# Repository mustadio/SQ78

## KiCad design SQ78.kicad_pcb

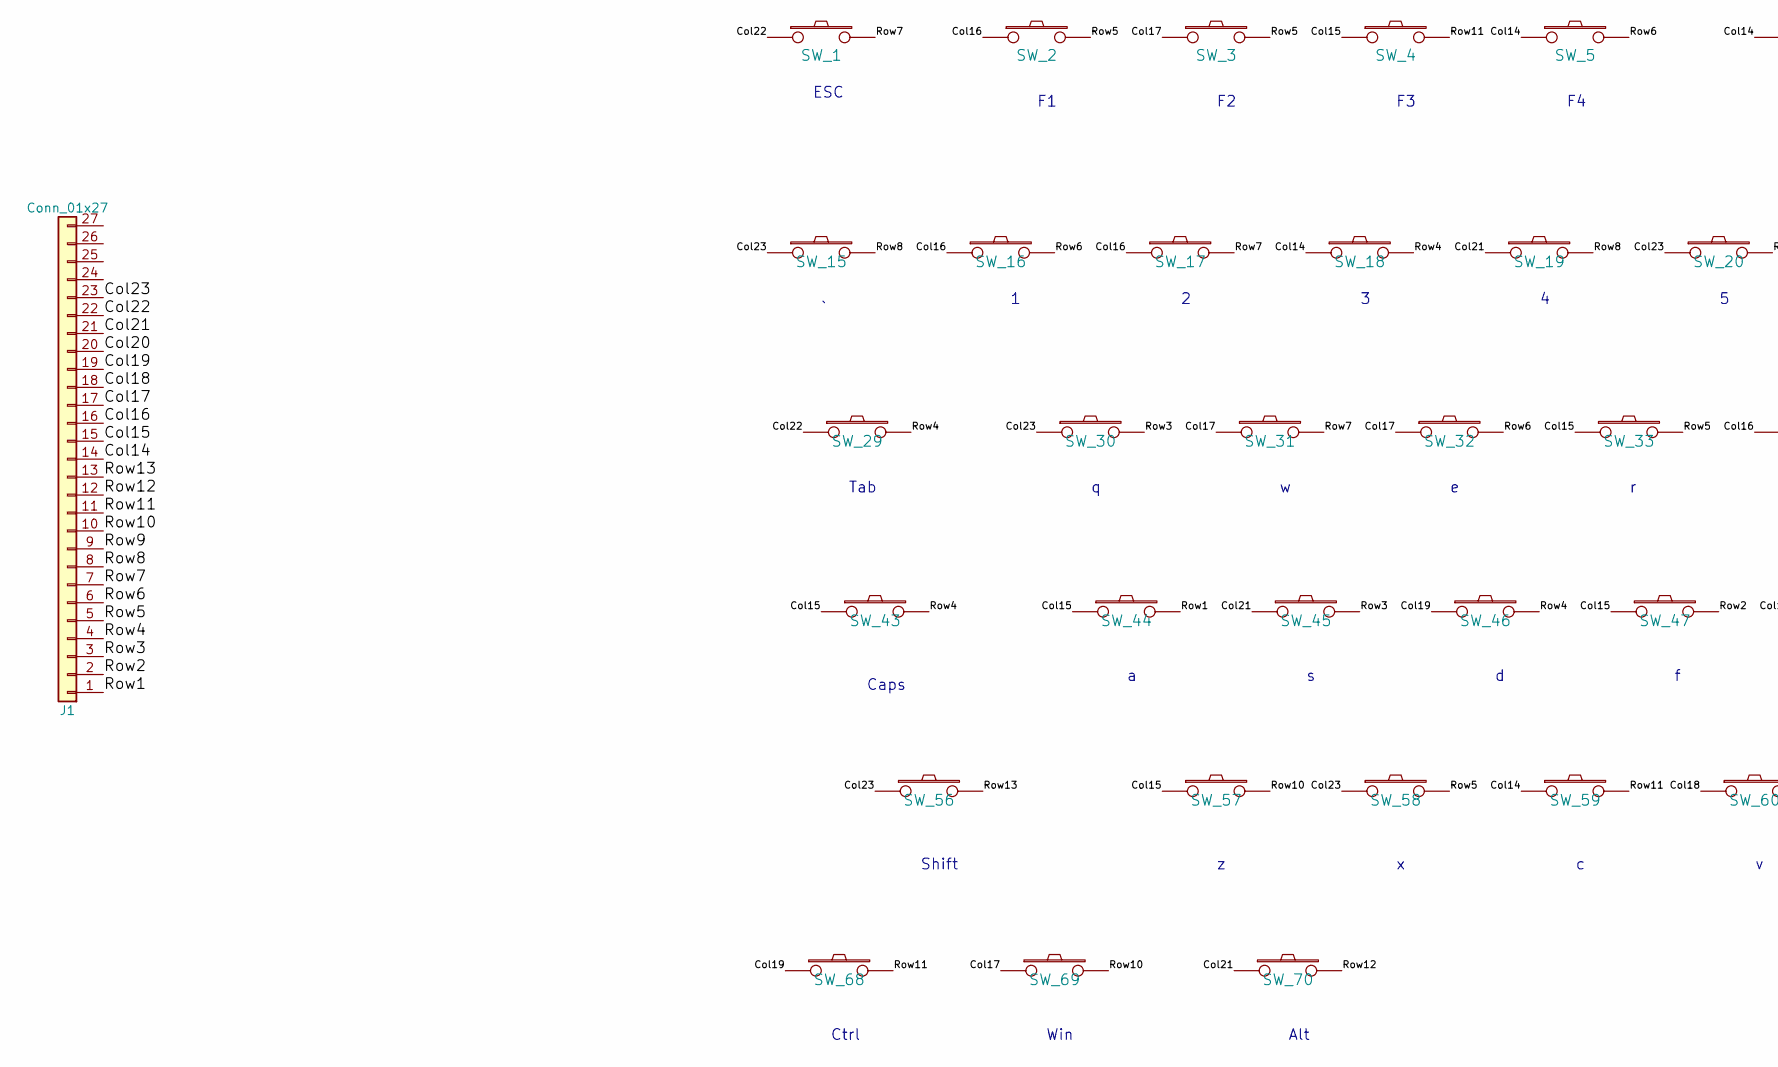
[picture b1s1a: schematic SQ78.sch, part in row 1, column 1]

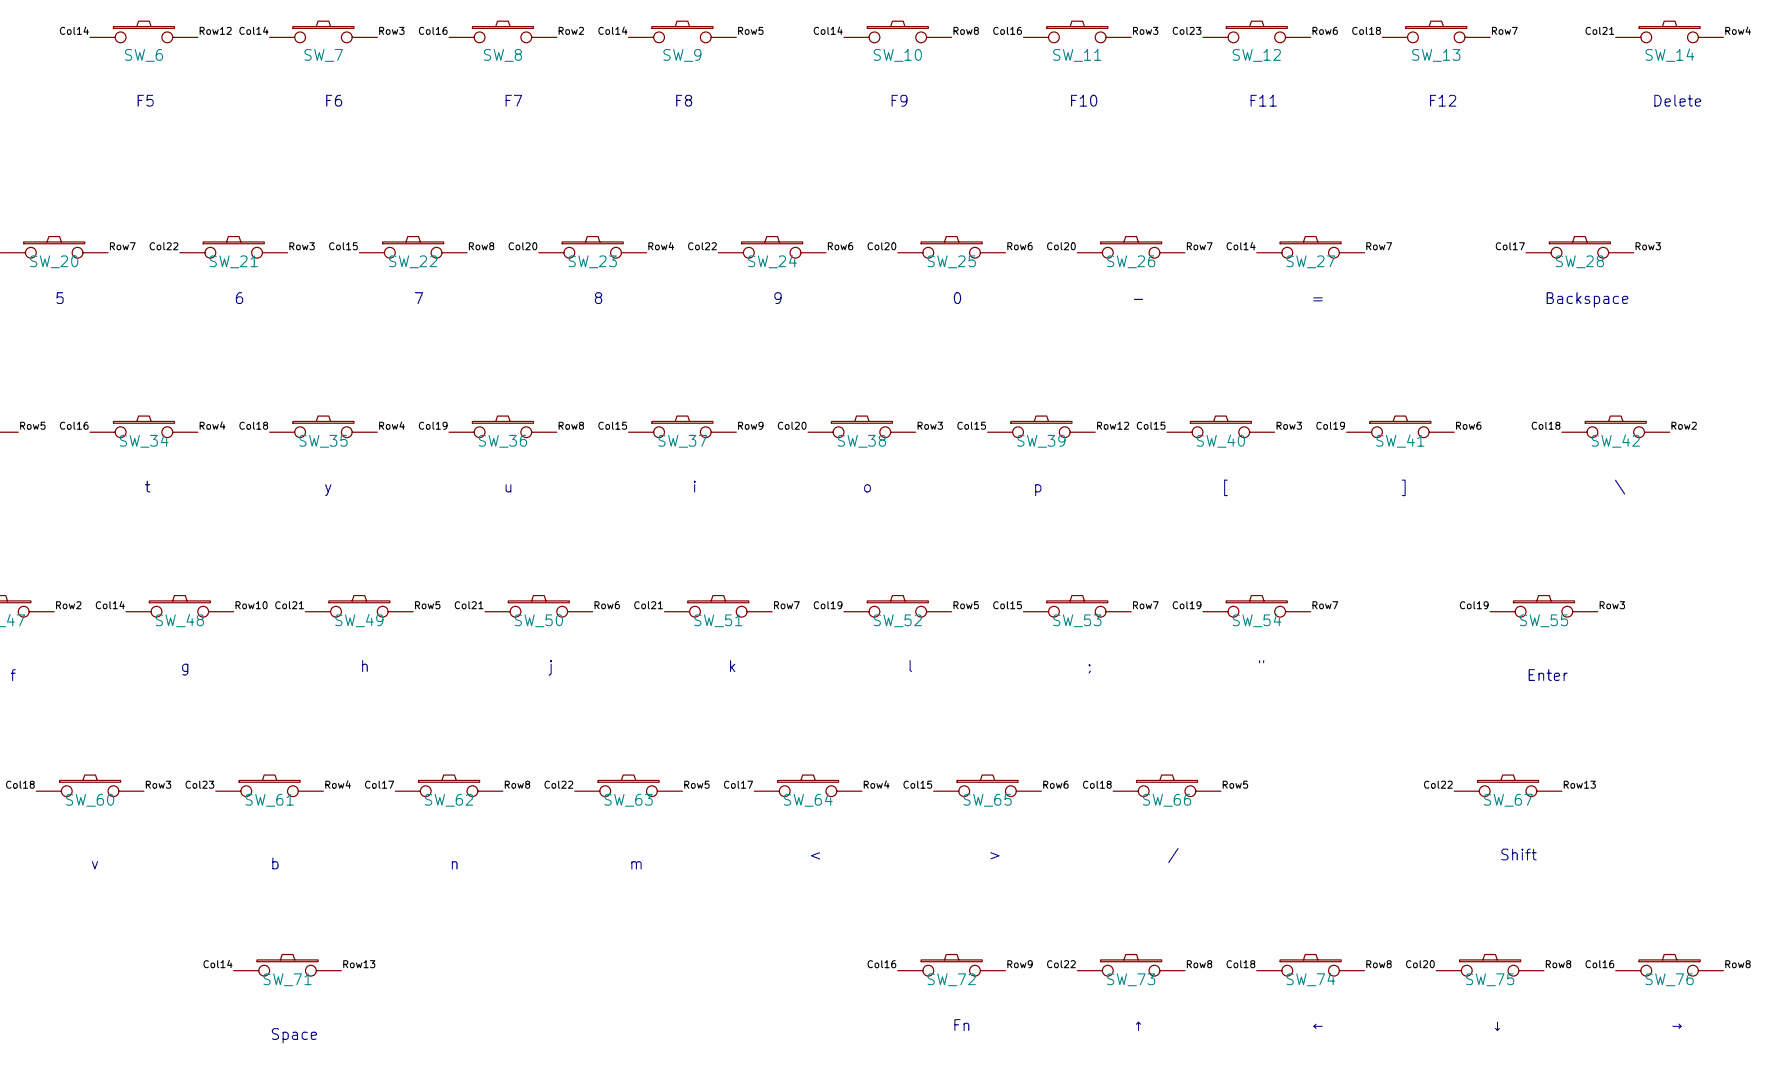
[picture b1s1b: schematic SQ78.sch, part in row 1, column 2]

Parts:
J1: Conn_01x27; TE_2-84953-7_1x27-1MP_P1.0mm_Horizontal
SW_1: ESC; CHERRY_PCB_100H
SW_2: F1; CHERRY_PCB_100H
SW_3: F2; CHERRY_PCB_100H
SW_4: F3; CHERRY_PCB_100H
SW_5: F4; CHERRY_PCB_100H
SW_6: F5; CHERRY_PCB_100H
SW_7: F6; CHERRY_PCB_100H
SW_8: F7; CHERRY_PCB_100H
SW_9: F8; CHERRY_PCB_100H
SW_10: F9; CHERRY_PCB_100H
SW_11: F10; CHERRY_PCB_100H
SW_12: F11; CHERRY_PCB_100H
SW_13: F12; CHERRY_PCB_100H
SW_14: Delete; CHERRY_PCB_100H
SW_15: CHERRY_PCB_100H
SW_16: 1; CHERRY_PCB_100H
SW_17: 2; CHERRY_PCB_100H
SW_18: 3; CHERRY_PCB_100H
SW_19: 4; CHERRY_PCB_100H
SW_20: 5; CHERRY_PCB_100H
SW_21: 6; CHERRY_PCB_100H
SW_22: 7; CHERRY_PCB_100H
SW_23: 8; CHERRY_PCB_100H
SW_24: 9; CHERRY_PCB_100H
SW_25: 0; CHERRY_PCB_100H
SW_26: -; CHERRY_PCB_100H
SW_27: =; CHERRY_PCB_100H
SW_28: Backspace; CHERRY_PCB_100H
SW_29: Tab; CHERRY_PCB_100H
SW_30: Q; CHERRY_PCB_100H
SW_31: W; CHERRY_PCB_100H
SW_32: E; CHERRY_PCB_100H
SW_33: R; CHERRY_PCB_100H
SW_34: T; CHERRY_PCB_100H
SW_35: Y; CHERRY_PCB_100H
SW_36: U; CHERRY_PCB_100H
SW_37: I; CHERRY_PCB_100H
SW_38: O; CHERRY_PCB_100H
SW_39: P; CHERRY_PCB_100H
SW_40: [; CHERRY_PCB_100H
SW_41: ]; CHERRY_PCB_100H
SW_42: \\; CHERRY_PCB_100H
SW_43: CAPS; CHERRY_PCB_100H
SW_44: A; CHERRY_PCB_100H
SW_45: S; CHERRY_PCB_100H
SW_46: D; CHERRY_PCB_100H
SW_47: F; CHERRY_PCB_100H
SW_48: G; CHERRY_PCB_100H
SW_49: H; CHERRY_PCB_100H
SW_50: J; CHERRY_PCB_100H
SW_51: K; CHERRY_PCB_100H
SW_52: L; CHERRY_PCB_100H
SW_53: ;; CHERRY_PCB_100H
SW_54: \"; CHERRY_PCB_100H
SW_55: Enter; CHERRY_PCB_100H
SW_56: LShift; CHERRY_PCB_100H
SW_57: Z; CHERRY_PCB_100H
SW_58: X; CHERRY_PCB_100H
SW_59: C; CHERRY_PCB_100H
SW_60: V; CHERRY_PCB_100H
SW_61: B; CHERRY_PCB_100H
SW_62: N; CHERRY_PCB_100H
SW_63: M; CHERRY_PCB_100H
SW_64: <; CHERRY_PCB_100H
SW_65: >; CHERRY_PCB_100H
SW_66: /; CHERRY_PCB_100H
SW_67: RShift; CHERRY_PCB_100H
SW_68: Ctrl; CHERRY_PCB_100H
SW_69: Win; CHERRY_PCB_100H
SW_70: Alt; CHERRY_PCB_100H
SW_71: Space; CHERRY_PCB_100H
SW_72: Fn; CHERRY_PCB_100H
SW_73: ↑; CHERRY_PCB_100H
SW_74: ←; CHERRY_PCB_100H
SW_75: ↓; CHERRY_PCB_100H
SW_76: →; CHERRY_PCB_100H

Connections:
/Col14: J1.14, SW_5.1, SW_6.1, SW_7.1, SW_9.1, SW_10.1, SW_18.1, SW_27.1, SW_48.1, SW_59.1, SW_71.1
/Col15: J1.15, SW_4.1, SW_22.1, SW_33.1, SW_37.1, SW_39.1, SW_40.1, SW_43.1, SW_44.1, SW_47.1, SW_53.1, SW_57.1, SW_65.1
/Col16: J1.16, SW_2.1, SW_8.1, SW_11.1, SW_16.1, SW_17.1, SW_34.1, SW_72.1, SW_76.1
/Col17: J1.17, SW_3.1, SW_28.1, SW_31.1, SW_32.1, SW_62.1, SW_64.1, SW_69.1
/Col18: J1.18, SW_13.1, SW_35.1, SW_42.1, SW_60.1, SW_66.1, SW_74.1
/Col19: J1.19, SW_36.1, SW_41.1, SW_46.1, SW_52.1, SW_54.1, SW_55.1, SW_68.1
/Col20: J1.20, SW_23.1, SW_25.1, SW_26.1, SW_38.1, SW_75.1
/Col21: J1.21, SW_14.1, SW_19.1, SW_45.1, SW_49.1, SW_50.1, SW_51.1, SW_70.1
/Col22: J1.22, SW_1.1, SW_21.1, SW_24.1, SW_29.1, SW_63.1, SW_67.1, SW_73.1
/Col23: J1.23, SW_12.1, SW_15.1, SW_20.1, SW_30.1, SW_56.1, SW_58.1, SW_61.1
/Row1: J1.1, SW_44.2
/Row2: J1.2, SW_8.2, SW_42.2, SW_47.2
/Row3: J1.3, SW_7.2, SW_11.2, SW_21.2, SW_28.2, SW_30.2, SW_38.2, SW_40.2, SW_45.2, SW_55.2, SW_60.2
/Row4: J1.4, SW_14.2, SW_18.2, SW_23.2, SW_29.2, SW_34.2, SW_35.2, SW_43.2, SW_46.2, SW_61.2, SW_64.2
/Row5: J1.5, SW_2.2, SW_3.2, SW_9.2, SW_33.2, SW_49.2, SW_52.2, SW_58.2, SW_63.2, SW_66.2
/Row6: J1.6, SW_5.2, SW_12.2, SW_16.2, SW_24.2, SW_25.2, SW_32.2, SW_41.2, SW_50.2, SW_65.2
/Row7: J1.7, SW_1.2, SW_13.2, SW_17.2, SW_20.2, SW_26.2, SW_27.2, SW_31.2, SW_51.2, SW_53.2, SW_54.2
/Row8: J1.8, SW_10.2, SW_15.2, SW_19.2, SW_22.2, SW_36.2, SW_62.2, SW_73.2, SW_74.2, SW_75.2, SW_76.2
/Row9: J1.9, SW_37.2, SW_72.2
/Row10: J1.10, SW_48.2, SW_57.2, SW_69.2
/Row11: J1.11, SW_4.2, SW_59.2, SW_68.2
/Row12: J1.12, SW_6.2, SW_39.2, SW_70.2
/Row13: J1.13, SW_56.2, SW_67.2, SW_71.2

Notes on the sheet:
ESC
Backspace
Tab
Caps
Enter
Shift
Ctrl
Win
Alt
Space
F10
Delete
F11
F12

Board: 2 copper layers, 77 parts (1 on the bottom side), 23 nets, no tracks yet.

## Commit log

2018-06-30 add edge and reversed MX
